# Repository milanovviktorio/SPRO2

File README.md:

# SPRO2
Electronics semester project 2

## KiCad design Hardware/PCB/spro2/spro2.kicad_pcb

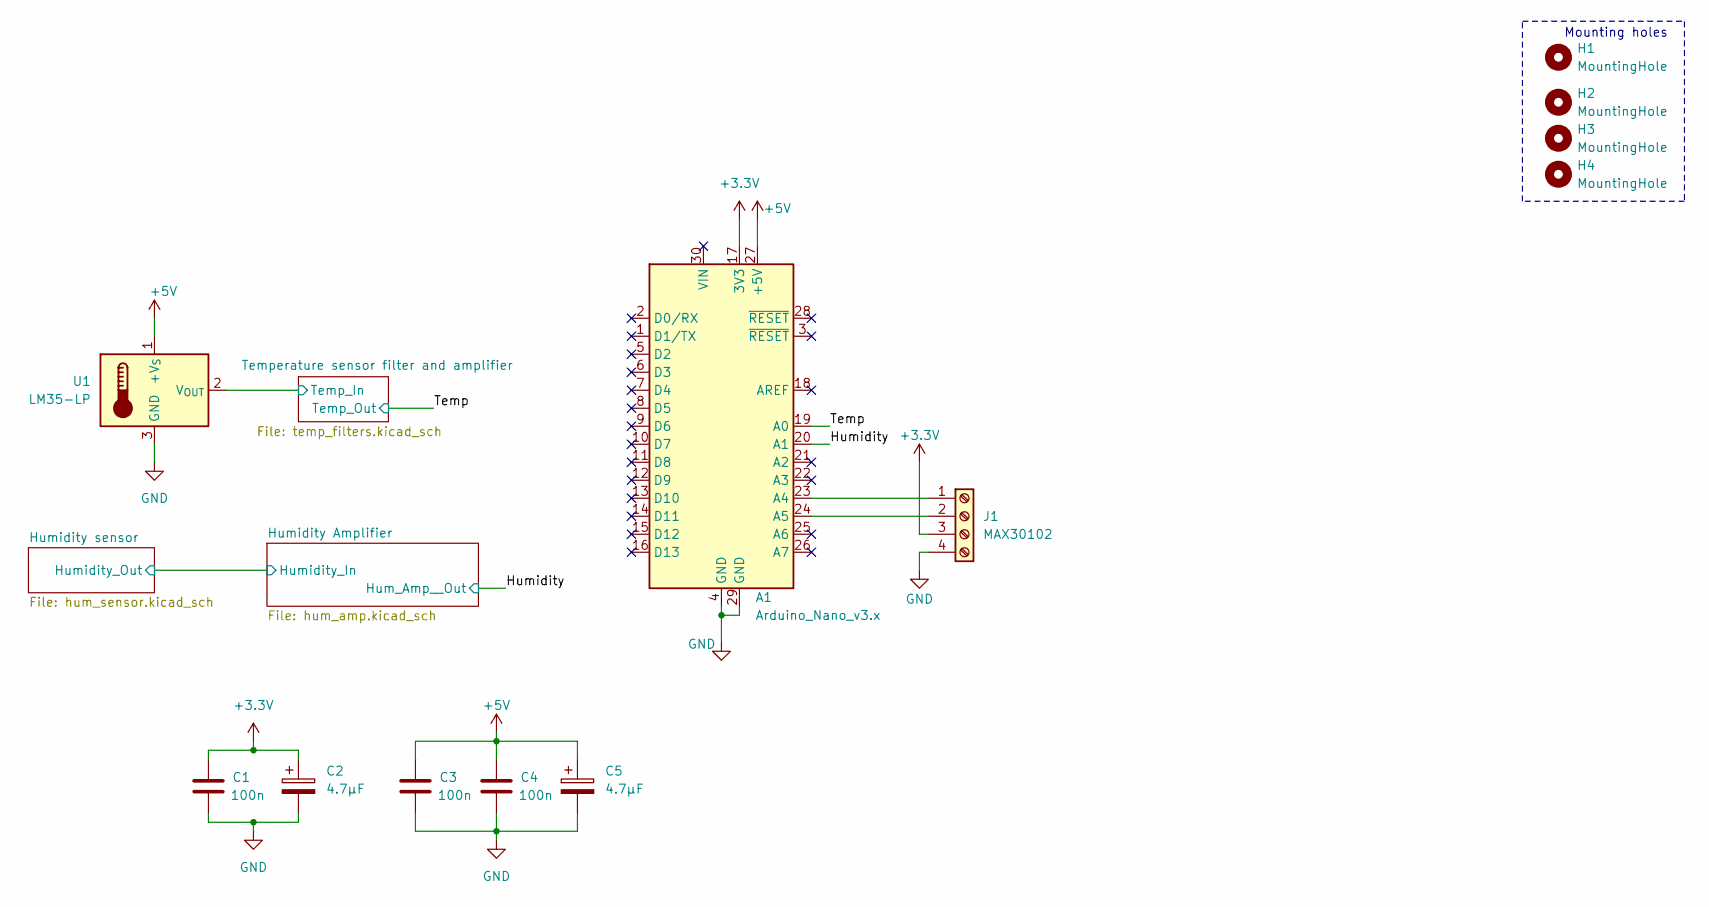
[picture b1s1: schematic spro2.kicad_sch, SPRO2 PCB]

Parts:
A1: Arduino_Nano_v3.x; Arduino_Nano
C1, C3, C4: 100n; C_Rect_L7.2mm_W2.5mm_P5.00mm_FKS2_FKP2_MKS2_MKP2
C2, C5: 4.7µF; CP_Radial_D7.5mm_P2.50mm
H1, H2, H3, H4: MountingHole; MountingHole_2.2mm_M2
J1: MAX30102; connector_4p
U1: LM35-LP; connector_3p

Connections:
+3.3V: A1.17 (3V3), C1.1, C2.1, J1.3
+5V: A1.27 (+5V), C3.1, C4.1, C5.1, U1.1 (+V_{S}); also elsewhere on the board
/Humidity: A1.20 (A1); also elsewhere on the board
/Temp: A1.19 (A0); also elsewhere on the board
/Temperature sensor filter and amplifier/Temp_In: U1.2 (V_{OUT}); also elsewhere on the board
GND: A1.4 (GND), A1.29 (GND), C1.2, C2.2, C3.2, C4.2, C5.2, J1.4, U1.3 (GND); also elsewhere on the board
unnamed: A1.23 (A4), J1.1
unnamed: A1.24 (A5), J1.2

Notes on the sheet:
Mounting holes

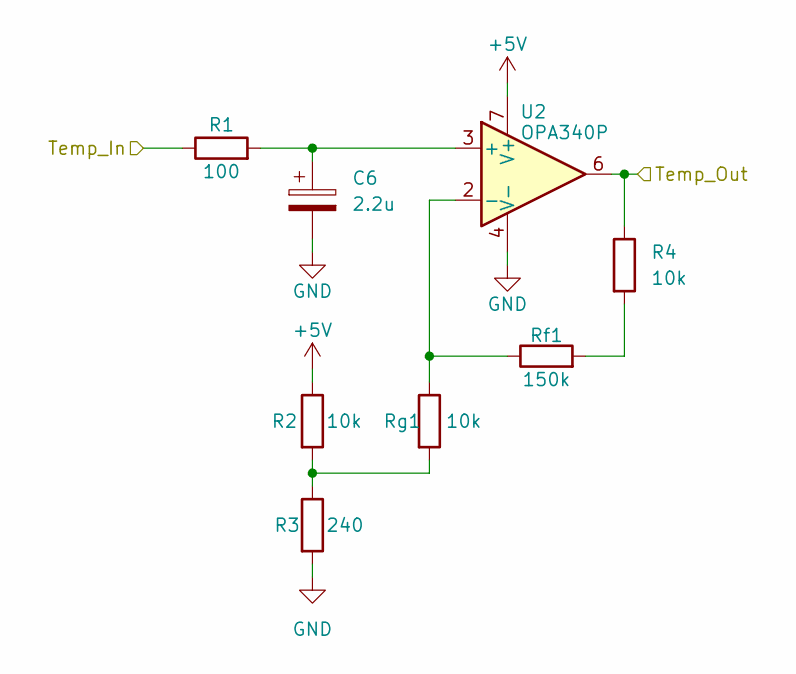
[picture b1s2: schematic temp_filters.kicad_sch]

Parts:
C6: 2.2u; CP_Radial_D6.3mm_P2.50mm
R1: 100; R_Axial_DIN0207_L6.3mm_D2.5mm_P10.16mm_Horizontal
R2, R4: 10k; R_Axial_DIN0207_L6.3mm_D2.5mm_P10.16mm_Horizontal
R3: 240; R_Axial_DIN0207_L6.3mm_D2.5mm_P10.16mm_Horizontal
Rf1: 150k; R_Axial_DIN0207_L6.3mm_D2.5mm_P10.16mm_Horizontal
Rg1: 10k; R_Axial_DIN0207_L6.3mm_D2.5mm_P10.16mm_Horizontal
U2: OPA340P; DIP-8_W7.62mm

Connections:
+5V: R2.1, U2.7 (V+); also elsewhere on the board
/Temp: R4.1, U2.6; also elsewhere on the board
/Temperature sensor filter and amplifier/Temp_In: R1.1; also elsewhere on the board
GND: C6.2, R3.2, U2.4 (V-); also elsewhere on the board
unnamed: R2.2, R3.1, Rg1.2
unnamed: R4.2, Rf1.2
unnamed: C6.1, R1.2, U2.3 (+)
unnamed: Rf1.1, Rg1.1, U2.2 (-)

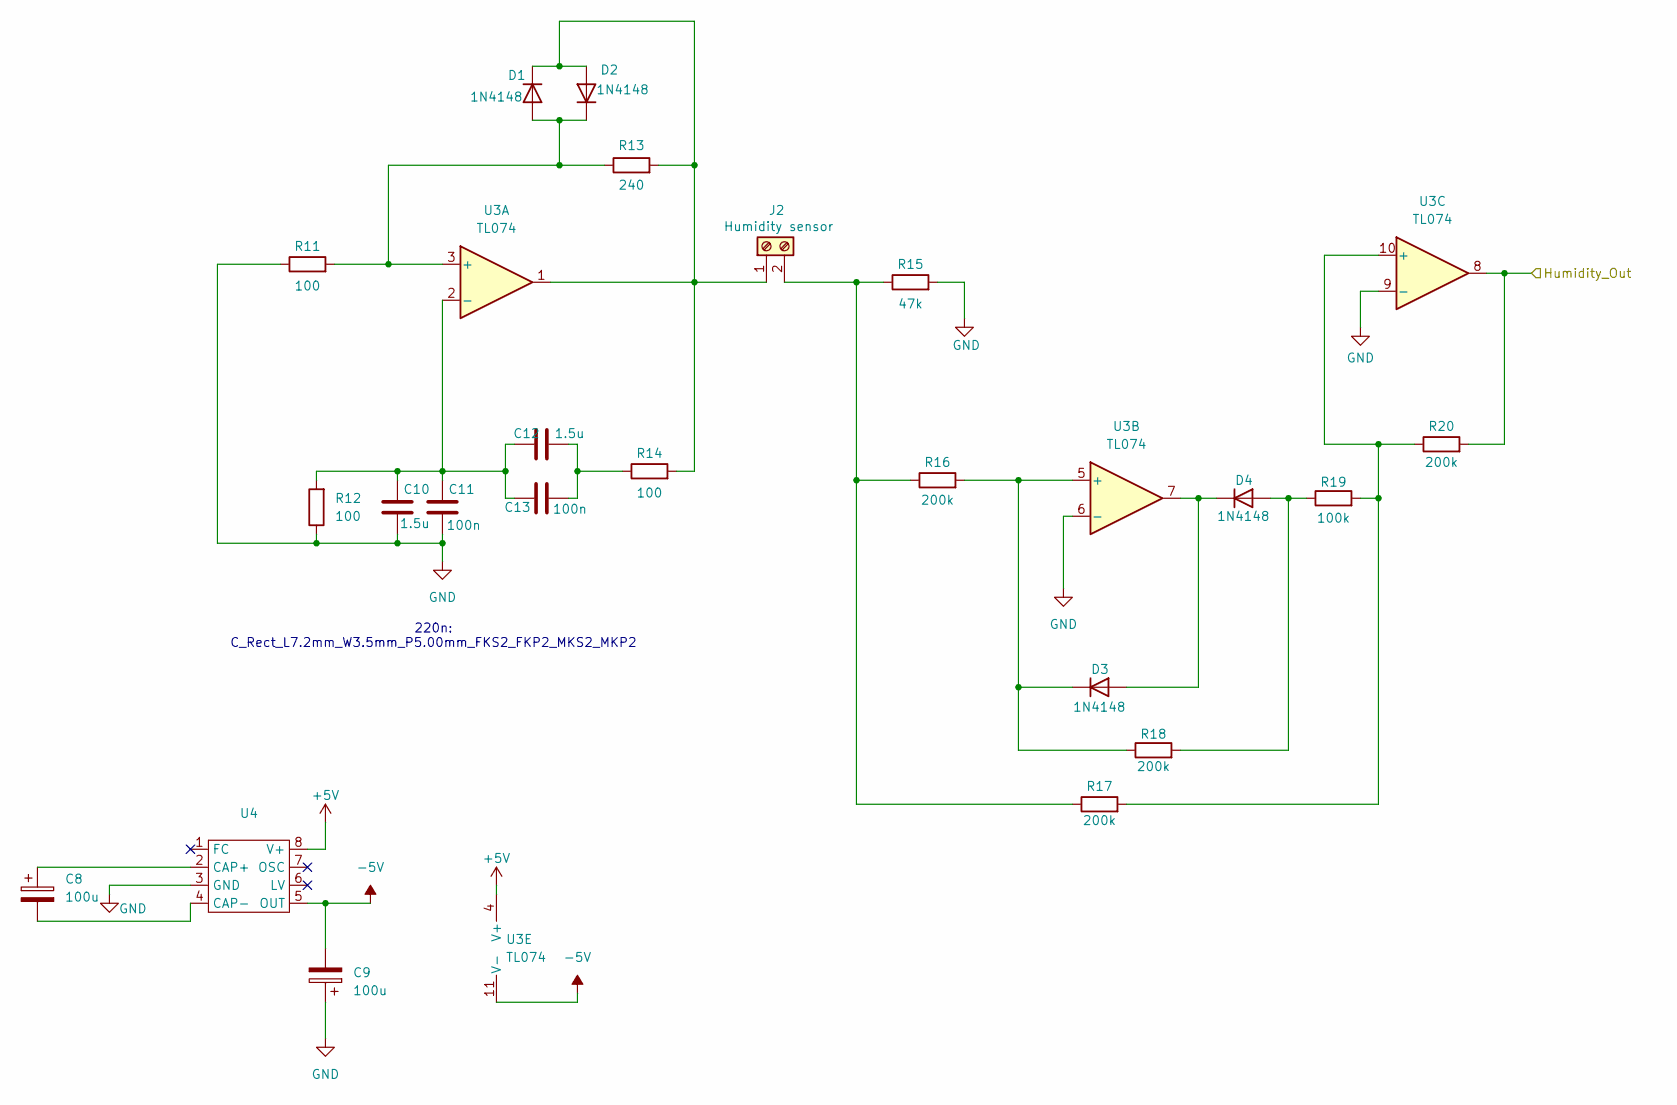
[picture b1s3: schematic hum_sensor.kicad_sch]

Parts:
C8, C9: 100u; CP_Radial_D10.0mm_P5.00mm
C10, C12: 1.5u; C_Rect_L13.0mm_W5.0mm_P10.00mm_FKS3_FKP3_MKS4
C11, C13: 100n; C_Rect_L7.2mm_W2.5mm_P5.00mm_FKS2_FKP2_MKS2_MKP2
D1, D2, D3, D4: 1N4148; D_DO-35_SOD27_P7.62mm_Horizontal
J2: Humidity sensor; connector_2p
R11, R12, R14: 100; R_Axial_DIN0207_L6.3mm_D2.5mm_P10.16mm_Horizontal
R13: 240; R_Axial_DIN0207_L6.3mm_D2.5mm_P10.16mm_Horizontal
R15: 47k; R_Axial_DIN0207_L6.3mm_D2.5mm_P10.16mm_Horizontal
R16, R17, R18, R20: 200k; R_Axial_DIN0207_L6.3mm_D2.5mm_P10.16mm_Horizontal
R19: 100k; R_Axial_DIN0207_L6.3mm_D2.5mm_P10.16mm_Horizontal
U3: TL074; DIP794W53P254L1930H508Q14N
U4: DIP-8_W7.62mm

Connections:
+5V: U3.4 (V+), U4.8 (V+); also elsewhere on the board
-5V: C9.2, U3.11 (V-), U4.5 (OUT)
/Humidity Amplifier/Humidity_In: R20.2, U3.8; also elsewhere on the board
GND: C9.1, C10.2, C11.2, R11.1, R12.1, R15.2, U3.6 (-), U3.9 (-), U4.3 (GND); also elsewhere on the board
unnamed: C12.1, C13.1, R14.1
unnamed: D1.2 (A), D2.1 (K), R11.2, R13.1, U3.3 (+)
unnamed: D1.1 (K), D2.2 (A), J2.1, R13.2, R14.2, U3.1
unnamed: D3.2 (A), D4.1 (K), U3.7
unnamed: D3.1 (K), R16.2, R18.1, U3.5 (+)
unnamed: D4.2 (A), R18.2, R19.1
unnamed: J2.2, R15.1, R16.1, R17.1
unnamed: C10.1, C11.1, C12.2, C13.2, R12.2, U3.2 (-)
unnamed: R17.2, R19.2, R20.1, U3.10 (+)
unnamed: C8.1, U4.2 (CAP+)
unnamed: C8.2, U4.4 (CAP-)

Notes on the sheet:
220n: C_Rect_L7.2mm_W3.5mm_P5.00mm_FKS2_FKP2_MKS2_MKP2

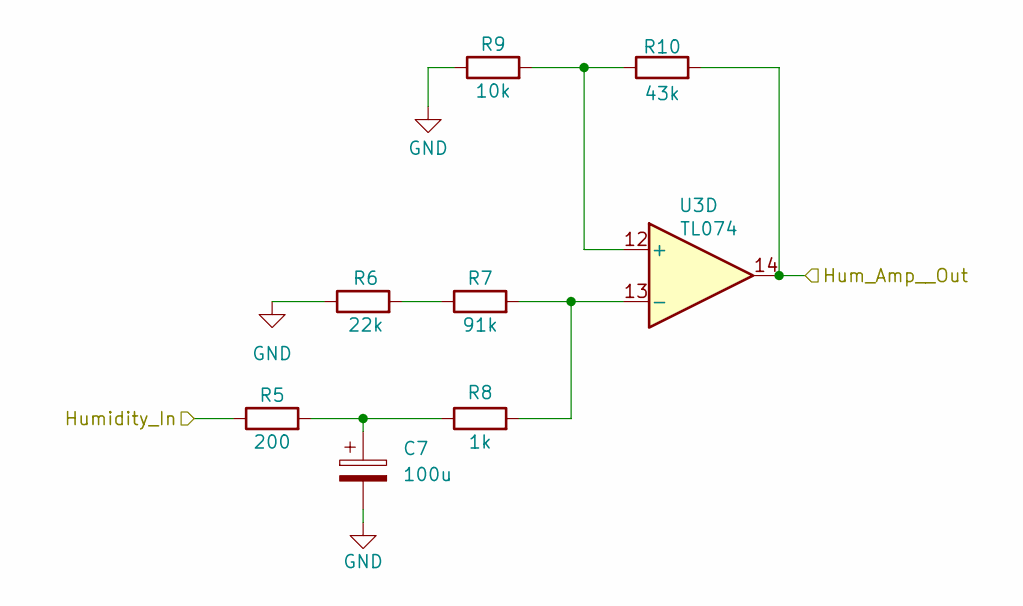
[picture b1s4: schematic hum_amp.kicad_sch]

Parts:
C7: 100u; CP_Radial_D10.0mm_P5.00mm
R5: 200; R_Axial_DIN0207_L6.3mm_D2.5mm_P10.16mm_Horizontal
R6: 22k; R_Axial_DIN0207_L6.3mm_D2.5mm_P10.16mm_Horizontal
R7: 91k; R_Axial_DIN0207_L6.3mm_D2.5mm_P10.16mm_Horizontal
R8: 1k; R_Axial_DIN0207_L6.3mm_D2.5mm_P10.16mm_Horizontal
R9: 10k; R_Axial_DIN0207_L6.3mm_D2.5mm_P10.16mm_Horizontal
R10: 43k; R_Axial_DIN0207_L6.3mm_D2.5mm_P10.16mm_Horizontal
U3: TL074; DIP794W53P254L1930H508Q14N

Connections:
/Humidity: R10.2, U3.14; also elsewhere on the board
/Humidity Amplifier/Humidity_In: R5.1; also elsewhere on the board
GND: C7.2, R6.1, R9.1; also elsewhere on the board
unnamed: C7.1, R5.2, R8.1
unnamed: R6.2, R7.1
unnamed: R9.2, R10.1, U3.12 (+)
unnamed: R7.2, R8.2, U3.13 (-)

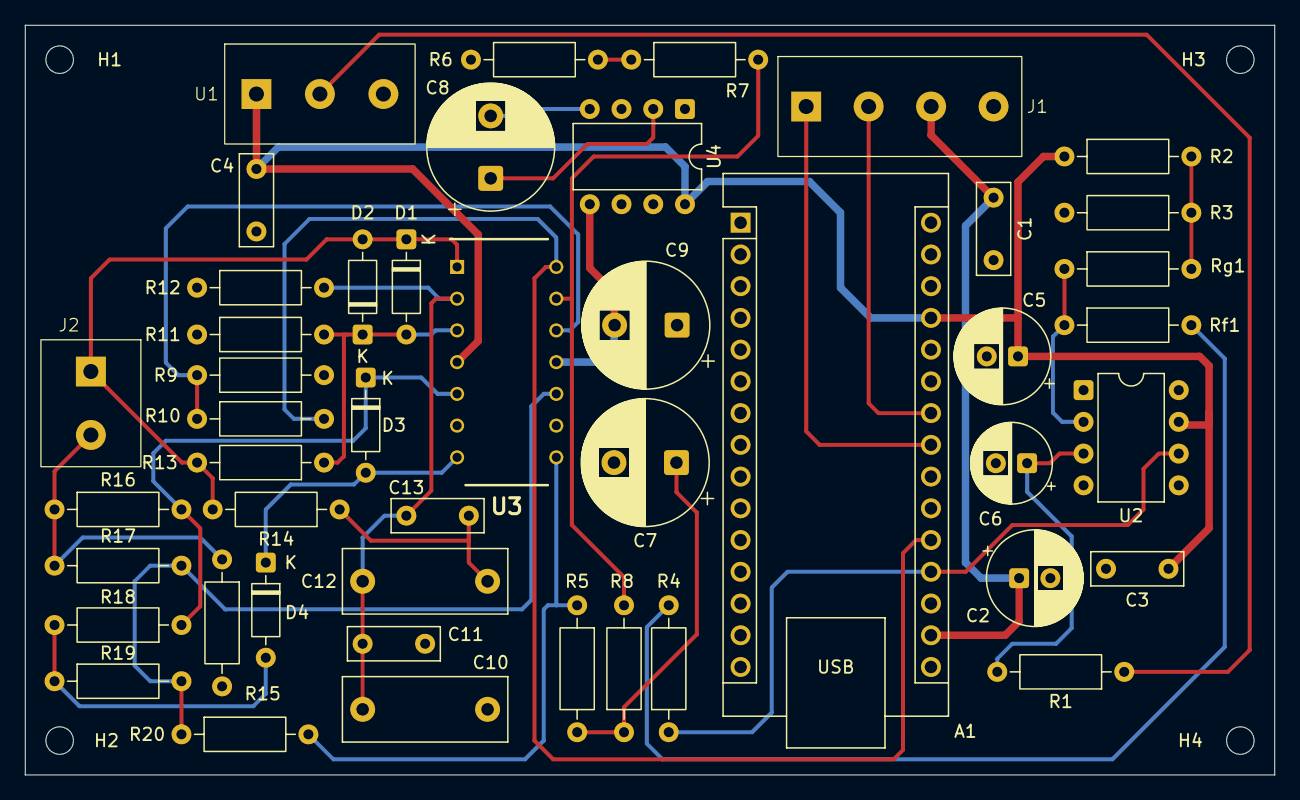
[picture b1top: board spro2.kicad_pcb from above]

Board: 2 copper layers, 100.0 x 60.0 mm, 50 parts (0 on the bottom side), 29 nets.

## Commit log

2025-03-28 initialization
2025-03-29 Added LTSpice simulations and a simulation for the temp sensor
2025-04-23 HR and SPO2 Trustworthiness is established
2025-04-23 Added the temperature schematics
2025-04-28 SPO2 functional
2025-04-28 test
2025-05-14 Updated circuit
2025-05-14 HR and SpO2 working
2025-05-15 Updated schematic and 1st version of the PCB
2025-05-15 Second version of the PCB
2025-05-16 Changes to humidity circuit. Add MAX660 circuit
2025-05-16 Temp scheme fixed
2025-05-16 Minor changes
2025-05-16 Temp circ fixed, added footprint for MAX6
2025-05-16 finish schematic
2025-05-16 Hopefully last version of PCB
2025-05-16 pcb finalized
2025-05-16 Added the footprints to library
2025-05-16 Finished PCB
2025-05-18 Working SpO2 + HR (no avg)
2025-05-20 add test code for humidity sensor
2025-05-20 full test code without stress var
2025-05-24 Update humidity test shit
2025-05-24 update humidity
2025-05-28 trustworthy calibration
2025-05-28 final code (needs testing for weights). no lcd yet
2025-05-29 ignat e pederas
2025-05-29 ignat e probit
2025-05-30 Added the LCD to schematic
2025-06-02 final code
2025-06-02 1000% final code I promise final final code promise trust final
    final
2025-06-02 Final scheamtic mega trust
2025-06-02 skibiduicide
